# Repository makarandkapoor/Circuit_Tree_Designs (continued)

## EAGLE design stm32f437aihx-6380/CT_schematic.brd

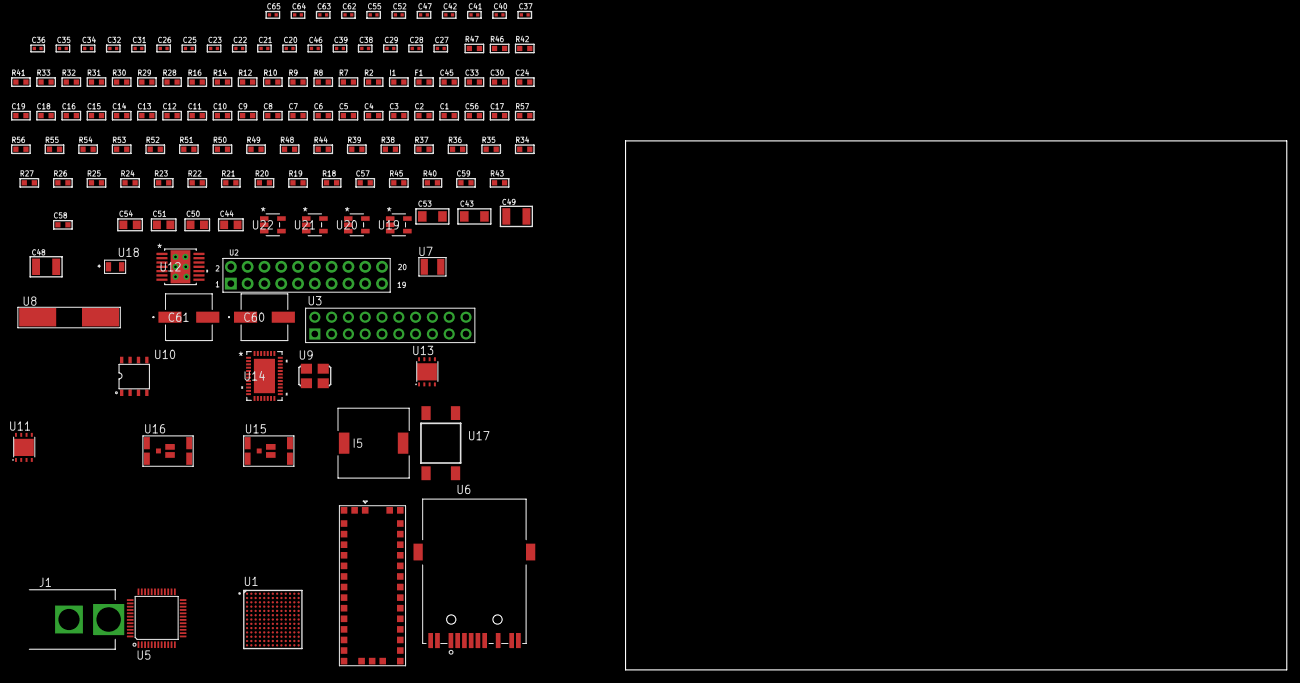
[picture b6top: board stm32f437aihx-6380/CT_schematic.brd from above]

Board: 2 copper layers, 100.0 x 80.0 mm, 139 parts (0 on the bottom side), 100 nets, no tracks yet.

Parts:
C1, C19, C24, C30, C33, C45: 1e-06; C0603
C2, C3, C4, C5, C6, C7, C8, C9, C10, C11, C12, C13, C14, C15, C16: 1e-07; C0603
C17: 4.7e-06; C0603
C18: 1e-08; C0603
C20, C21, C25, C26, C31, C34, C36, C37, C47, C55: 1e-07; C0402
C22, C23: 1e-11; C0402
C27, C28: 2.2e-11; C0402
C29: 2.2e-08; C0402
C32, C35, C40, C41, C42, C52, C62, C63, C64, C65: 1e-08; C0402
C38, C39: 2.7e-11; C0402
C43, C53: 1e-05; C1206
C44, C50, C51, C54: 1e-05; C0805
C46: 3.3e-09; C0402
C48, C49: 2.2e-05; C1210
C56: 2.2e-06; C0603
C57: 2.45e-08; R0603
C58: 2.8258362168397e-09; R0603
C59: 7.105e-09; R0603
C60, C61: 0.0001; EXV-9H
F1: 240.0; L0603
I1: 97.0; R0603
I5: 2.5e-06; DR1040
J1: PJ-037B; PJ-037B_PACKAGE
R2, R42, R47: 1000.0; R0603
R7, R8, R9, R33: 4700.0; R0603
R10, R12, R14, R16: 2200.0; R0603
R18, R19, R20, R21, R22, R23, R24, R25, R26, R27, R34, R35, R36, R37, R38, R39, R48, R50, R51, R54, R55, R56: 10000.0; R0603
R28, R29: 0.1; R0603
R30, R31, R41, R46: 200.0; R0603
R32: 2490.0; R0603
R40, R45: 100000.0; R0603
R43: 71007.101651032; R0603
R44: 22000.0; R0603
R49: 75000.0; R0603
R52, R53: 95300.0; R0603
R57: 48900.0; R0603
U1: STM32F437AIH6; UFBGA169
U2: arducam_ov2640; ARDUCAM
U3: TST-110-05-T-D-RA
U4: M10382
U5: RTL8201FL-VB-CG
U6: 7498011122R
U7: ABS07-32.768KHZ-7-T
U8: ABLS-25.000MHZ-B2F-T
U9: ASFL1-25MHZ-NCS; ASFL1
U10: idt74fct38072; IDT74FCT38072
U11, U13: LP3878SDX-ADJ/NOPB; WSON-8
U12: tps54325PWP; HTSSOP14
U14: LTC2928CUHF#PBF; QFN-38_UHF
U15, U16: IRF8306MTRPbF; IRF8306MTRPBF
U17: 4-1437565-2; SW_4-1437565-2
U18: Q65110A2395; LGM67K-G1J2-24-Z
U19, U20, U21, U22: nc7sz125m5x; NC7SZ125M5X

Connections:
CLK_CRYSTAL_U1_E1: C22.1, U1.E1, U7.1
CLK_CRYSTAL_U1_F1: C23.1, U1.F1, U7.2
CLK_CRYSTAL_U5_42: C39.1, U5.42, U8.1
CLK_CRYSTAL_U5_43: C38.1, U5.43, U8.2
CLK_U1_G2: U1.G2, U10.6
CLK_U2_8: U2.8, U10.7
CLK_U10_3: U9.3, U10.3
GND: C1.2, C2.2, C3.2, C4.2, C5.2, C6.2, C7.2, C8.2, C9.2, C10.2, C11.2, C12.2, C13.2, C14.2, C15.2, C16.2, C17.2, C18.2, C19.2, C20.2, C21.2, C22.2, C23.2, C24.2, C25.2, C26.2, C27.2, C28.2, C29.2, C30.2, C31.2, C32.2, C33.2, C34.2, C35.2, C36.2, C37.2, C38.2, C39.2, C40.2, C41.2, C42.2, C43.2, C44.2, C45.2, C46.2, C48.2, C49.2, C50.2, C51.2, C52.2, C53.2, C54.2, C55.2, C56.2, C57.2, C58.2, C59.2, C60.2, C61.2, C62.2, C63.2, C64.2, C65.2, J1.2, R2.2, R20.2, R27.2, R28.2, R29.2, R32.2, R34.2, R36.2, R37.2, R38.2, R39.2, R42.2, R44.2, R47.2, R49.2, R52.2, R53.2, R54.2, R55.2, R56.2, U1.D7, U1.D11, U1.E7, U1.F5, U1.F6, U1.G7, U1.G9, U1.J1, U1.J2, U1.J6, U1.J7, U1.J10, U2.2, U2.20, U3.4, U3.6, U3.8, U3.10, U3.12, U3.14, U3.16, U3.18, U3.20, U4.2, U4.4, U4.14, U4.17, U4.21, U4.24, U4.26, U4.28, U4.33, U4.34, U4.35, U4.36, U5.7, U5.20, U5.33, U5.47, U6.11, U9.2, U10.4, U10.5, U10.8, U11.3, U11.PAD, U12.5, U12.8, U12.9, U12.15, U13.3, U13.PAD, U14.8, U14.9, U14.10, U14.12, U14.13, U14.24, U14.25, U14.30, U14.32, U14.39, U18.C, U19.2, U19.3, U20.1, U20.3, U21.1, U21.3, U22.1, U22.3
NET_U1_A5: R19.1, U1.A5
NET_U1_B5: R12.1, U1.B5, U4.18
NET_U1_C3: R18.1, U1.C3
NET_U1_C5: R10.1, U1.C5, U4.19
NET_U1_D12: C21.1, U1.D12
NET_U1_H2: R8.1, U1.H2, U21.4
NET_U1_H5: R14.1, U1.H5, U5.30
NET_U1_J4: C18.1, C19.1, F1.1, U1.J3, U1.J4
NET_U1_K2: R16.1, U1.K2, U5.31
NET_U1_L5: R20.1, U1.L5
NET_U1_M1: R21.1, U1.M1
NET_U1_N11: U17.3, U17.4
NET_U2_19: R9.1, U2.19, U22.4
NET_U3_19: R27.1, U3.19
NET_U5_6: C30.1, C31.1, C32.1, I1.1, U5.6, U5.41
NET_U5_10: R37.1, U5.10
NET_U5_29: R7.1, U5.29, U20.4
NET_U5_32: R33.1, U5.32
NET_U5_34: R35.1, U5.34
NET_U5_35: R36.1, U5.35
NET_U5_40: C37.1, U5.40
NET_U5_46: R32.1, U5.46
NET_U5_48: C36.1, U5.48
NET_U6_1: U5.1, U6.1
NET_U6_3: U5.2, U6.3
NET_U6_4: U5.4, U6.4
NET_U6_5: C29.1, U6.2, U6.5
NET_U6_6: U5.5, U6.6
NET_U6_8: R29.1, U6.8
NET_U6_10: R30.1, U6.10
NET_U6_12: R31.1, U6.12
NET_U6_13: R28.1, U6.13, U6.14
NET_U11_1: C42.1, U11.1
NET_U11_6: R41.2, R42.1, U11.6
NET_U11_8: R40.1, U11.8
NET_U12_2: R43.2, R44.1, U12.2
NET_U12_3: C45.1, U12.3
NET_U12_4: C46.1, U12.4
NET_U12_10: C47.1, I5.1, U12.10, U12.11
NET_U12_12: C47.2, U12.12
NET_U13_1: C52.1, U13.1
NET_U13_6: R46.2, R47.1, U13.6
NET_U13_8: R45.1, U13.8
NET_U14_3: R55.1, U14.3
NET_U14_6: R52.1, U14.6
NET_U14_7: R53.1, U14.7
NET_U14_16: R54.1, R57.1, U14.16
NET_U14_18: R51.1, U14.18
NET_U14_19: R50.1, U14.19, U14.20
NET_U14_21: R48.1, R49.1, U14.21, U19.4, U20.2, U21.2, U22.2
NET_U14_26: C58.1, U14.26
NET_U14_27: C57.1, U14.27
NET_U14_28: C59.1, U14.28
NET_U14_38: R56.1, U14.38
NET_U15_3: U14.2, U15.3
NET_U16_3: U14.37, U16.3
NET_U17_1: R2.1, U17.1, U17.2
PROC_DCMI_D0: U1.E8, U2.18
PROC_DCMI_D1: U1.E9, U2.17
PROC_DCMI_D2: U1.B4, U2.16
PROC_DCMI_D3: U1.A4, U2.15
PROC_DCMI_D4: U1.B10, U2.14
PROC_DCMI_D5: U1.A9, U2.13
PROC_DCMI_D6: U1.A2, U2.12
PROC_DCMI_D7: U1.B1, U2.11
PROC_DCMI_D8: U1.C10, U2.10
PROC_DCMI_D9: U1.A10, U2.9
PROC_DCMI_HSYNC: U1.L10, U2.6
PROC_DCMI_PIXCK: U1.N3, U2.7
PROC_DCMI_VSYNC: U1.A3, U2.5
PROC_ETH_COL: U1.K3, U5.38
PROC_ETH_CRS: U1.L2, U5.36
PROC_ETH_RXD3: R38.1, U1.K5, U5.18
PROC_ETH_RX_CLK: U1.K1, U5.19
PROC_ETH_RX_DV: R34.1, U1.K4, U5.13
PROC_ETH_RX_ER: R39.1, U1.E3, U5.39
PROC_ETH_TXD2: U1.H6, U5.25
PROC_ETH_TXD3: U1.B2, U5.26
PROC_ETH_TX_CLK: U1.H7, U5.22
PROC_ETH_TX_EN: U1.B7, U5.27
PROC_SYS_JTCK_SWCLK: R25.1, U1.A11, U3.9
PROC_SYS_JTDI: R23.1, U1.B11, U3.5
PROC_SYS_JTDO_SWO: U1.B6, U3.13
PROC_SYS_JTMS_SWDIO: R24.1, U1.E12, U3.7
PROC_SYS_JTRST: R22.1, U1.A6, U3.3
RST_OUT_U3_SRESET_B: R26.1, U3.15, U19.1
VCC_6V4: C55.1, C56.1, C60.1, C61.1, J1.1, R48.2, R50.2, R51.2, R57.2, U14.11, U14.22, U15.1, U15.2, U15.6, U15.7, U16.1, U16.2, U16.6, U16.7
VCC_S1_6V4: C43.1, C50.1, C51.1, R40.2, U11.4, U12.7, U12.13, U12.14, U15.4, U15.5
VCC_S2_6V4: C53.1, R45.2, U13.4, U16.4, U16.5
VCC_TIER1_1V2: C20.1, C44.1, R41.1, U1.N9, U11.5
VCC_TIER1_3V3: C1.1, C2.1, C3.1, C4.1, C5.1, C6.1, C7.1, C8.1, C9.1, C10.1, C11.1, C12.1, C13.1, C14.1, C15.1, C16.1, C17.1, C24.1, C25.1, C26.1, C27.1, C28.1, C33.1, C34.1, C35.1, C40.1, C41.1, C48.1, C49.1, C62.1, C63.1, C64.1, C65.1, F1.2, I1.2, I5.2, R7.2, R8.2, R9.2, R10.2, R12.2, R14.2, R16.2, R18.2, R19.2, R21.2, R22.2, R23.2, R24.2, R25.2, R26.2, R33.2, R35.2, R43.1, U1.D3, U1.D6, U1.D10, U1.E5, U1.E6, U1.F4, U1.F7, U1.F8, U1.G8, U1.G10, U1.H4, U1.H8, U1.J11, U1.K6, U1.L6, U2.1, U3.1, U3.2, U4.5, U4.25, U4.27, U5.15, U5.21, U5.37, U9.4, U10.1, U10.2, U12.1, U19.5, U20.5, U21.5, U22.5
VCC_TIER2_1V2: C54.1, R46.1, U13.5

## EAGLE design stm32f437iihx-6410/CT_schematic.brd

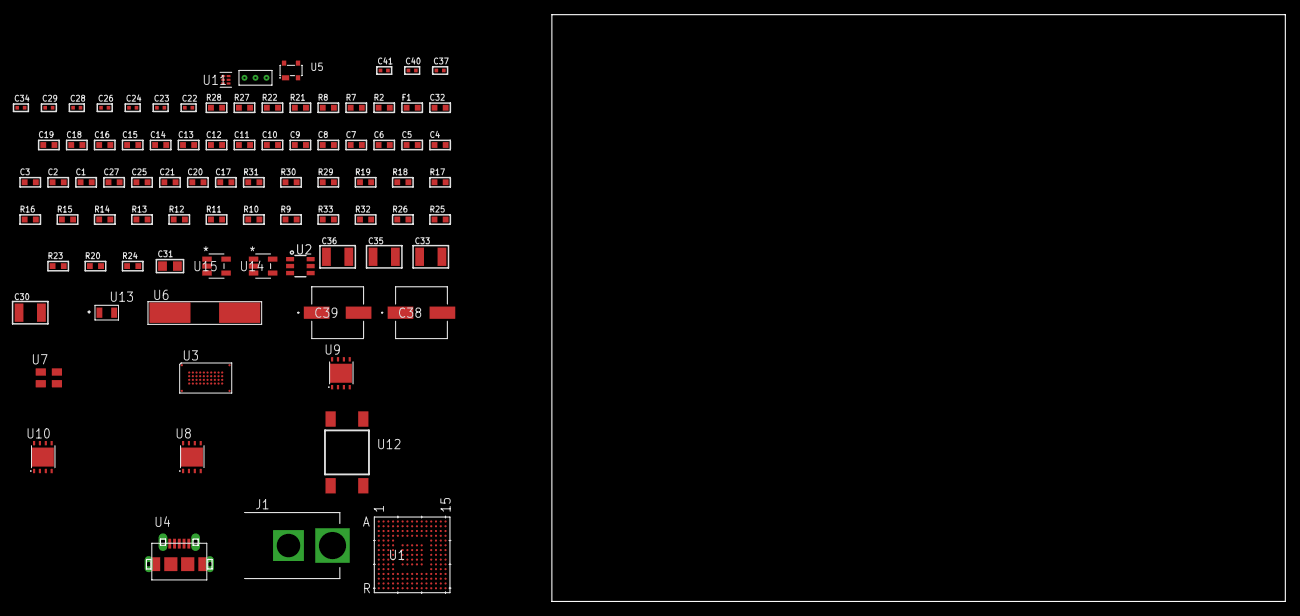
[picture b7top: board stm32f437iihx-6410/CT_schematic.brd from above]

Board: 2 copper layers, 87 parts (0 on the bottom side), 69 nets, no tracks yet.

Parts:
C1, C19: 1e-06; C0603
C2, C3, C4, C5, C6, C7, C8, C9, C10, C11, C12, C13, C14, C15, C16: 1e-07; C0603
C17: 4.7e-06; C0603
C18: 1e-08; C0603
C20, C21, C25, C27: 2.2e-06; C0603
C22, C23: 1e-11; C0402
C24, C26, C37: 1e-07; C0402
C28, C29, C34, C40, C41: 1e-08; C0402
C30, C33, C35, C36: 1e-05; C1210
C31: 1e-05; C0805
C32: 8e-07; R0603
C38, C39: 0.0001; EXV-9H
F1: 240.0; L0603
J1: PJ-037B; PJ-037B_PACKAGE
R2, R22, R28: 1000.0; R0603
R7, R8: 4700.0; R0603
R9: 47000.0; R0603
R10, R11, R12, R13, R14, R15, R16, R17, R18, R19, R29, R30: 10000.0; R0603
R20, R23, R25, R26: 100000.0; R0603
R21: 806.0; R0603
R24: 153694.38; R0603
R27: 3900.0; R0603
R31: 82000.0; R0603
R32: 300000.0; R0603
R33: 120000.0; R0603
U1: STM32F437IIH6; UFBGA176_25
U2: MAX4995AAUT+T; SOT-23-6
U3: S29VS256RABBHW000
U4: 47590-0001; MICRO_USB_AB
U5: prtr5v0u2ax; SOT143B
U6: ABLS-25.000MHZ-B2F-T
U7: ASEK-32.768KHz-ECST; ASEK
U8, U10: LP3878SDX-ADJ/NOPB; WSON-8
U9: LP2951ACSDX/NOPB; WSON-8
U11: TPS3895ADRYR; SON-6
U12: 4-1437565-2; SW_4-1437565-2
U13: Q65110A2395; LGM67K-G1J2-24-Z
U14, U15: nc7sz125m5x; NC7SZ125M5X
U16: Dummy; DUMMY_PACKAGE_185

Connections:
CLK_CRYSTAL_U1_G1: C22.1, U1.G1, U6.1
CLK_CRYSTAL_U1_H1: C23.1, U1.H1, U6.2
CLK_U1_E1: U1.E1, U7.3
GND: C1.2, C2.2, C3.2, C4.2, C5.2, C6.2, C7.2, C8.2, C9.2, C10.2, C11.2, C12.2, C13.2, C14.2, C15.2, C16.2, C17.2, C18.2, C19.2, C20.2, C21.2, C22.2, C23.2, C24.2, C25.2, C26.2, C27.2, C28.2, C29.2, C30.2, C31.2, C32.2, C33.2, C34.2, C35.2, C36.2, C37.2, C38.2, C39.2, C40.2, C41.2, J1.2, R2.2, R9.2, R13.2, R15.2, R22.2, R25.2, R28.2, R31.2, R33.2, U1.D5, U1.D7, U1.D8, U1.D9, U1.F2, U1.F6, U1.F7, U1.F8, U1.F9, U1.F10, U1.F12, U1.G2, U1.G6, U1.G7, U1.G8, U1.G9, U1.G10, U1.G12, U1.H6, U1.H7, U1.H8, U1.H9, U1.H10, U1.H12, U1.J6, U1.J7, U1.J8, U1.J9, U1.J10, U1.K6, U1.K7, U1.K8, U1.K9, U1.K10, U1.M1, U1.M8, U1.M9, U1.N1, U2.2, U3.C5, U3.D12, U3.E3, U3.F5, U4.5, U4.6, U4.7, U4.8, U4.9, U5.1, U7.2, U8.3, U8.PAD, U9.3, U9.4, U9.PAD, U10.3, U10.PAD, U11.2, U13.C, U14.1, U14.3, U15.1, U15.3, U16.1
NET_U1_C6: R10.1, U1.C6
NET_U1_D6: R11.1, U1.D6
NET_U1_F13: C21.1, U1.F13
NET_U1_J1: R8.1, U1.J1, U15.4
NET_U1_L4: R13.1, U1.L4
NET_U1_M6: R12.1, U1.M6
NET_U1_M10: C20.1, U1.M10
NET_U1_R1: C18.1, C19.1, F1.1, U1.P1, U1.R1
NET_U1_R15: U12.3, U12.4
NET_U2_3: R9.1, U2.3
NET_U3_D8: R7.1, U3.D8, U14.4
NET_U8_1: C29.1, U8.1
NET_U8_6: R21.2, R22.1, U8.6
NET_U8_8: R20.1, U8.8
NET_U9_5: R23.1, U9.5
NET_U9_7: R24.2, R25.1, U9.7
NET_U10_1: C34.1, U10.1
NET_U10_6: R27.2, R28.1, U10.6
NET_U10_8: R26.1, U10.8
NET_U11_1: R30.1, R31.1, U11.1
NET_U11_3: R32.2, R33.1, U11.3
NET_U11_4: R29.1, U11.4, U14.2, U15.2
NET_U12_1: R2.1, U12.1, U12.2
PROC_ADC1_IN3: U1.R2, U16.2
PROC_ADC1_IN4: U1.N4, U16.3
PROC_FMC_A16: U1.N14, U3.D4
PROC_FMC_A17: U1.N13, U3.C11
PROC_FMC_A18: U1.M15, U3.D10
PROC_FMC_A19: U1.A1, U3.C10
PROC_FMC_A20: U1.B1, U3.D5
PROC_FMC_A21: U1.B2, U3.C4
PROC_FMC_A22: U1.B3, U3.C12
PROC_FMC_A23: U1.A2, U3.D7
PROC_FMC_CLK: U1.D11, U3.C6
PROC_FMC_D0: U1.M14, U3.F3
PROC_FMC_D1: U1.L14, U3.F4
PROC_FMC_D2: U1.B12, U3.E6
PROC_FMC_D3: U1.C12, U3.E7
PROC_FMC_D4: U1.R8, U3.F8
PROC_FMC_D5: U1.P8, U3.F9
PROC_FMC_D6: U1.P9, U3.E10
PROC_FMC_D7: U1.R9, U3.E11
PROC_FMC_D8: U1.P10, U3.E4
PROC_FMC_D9: U1.R10, U3.E5
PROC_FMC_D10: U1.N11, U3.F6
PROC_FMC_D11: U1.P11, U3.F7
PROC_FMC_D12: U1.R11, U3.E8
PROC_FMC_D13: U1.P15, U3.E9
PROC_FMC_D14: U1.P14, U3.F11
PROC_FMC_D15: U1.N15, U3.F12
PROC_FMC_NE2: R17.1, U1.C10, U3.D11
PROC_FMC_NL: U1.B5, U3.D6
PROC_FMC_NOE: R19.1, U1.D10, U3.E12
PROC_FMC_NWAIT: R16.1, U1.B11, U3.C3
PROC_FMC_NWE: R18.1, U1.C11, U3.C8
PROC_GPIO_TO_U1_USB_FAULT: R14.1, U1.A4, U2.6
PROC_GPIO_TO_U1_VBUS_EN: R15.1, U1.A3, U2.4
PROC_USB_OTG_FS_DM: U1.C15, U4.2, U5.3
PROC_USB_OTG_FS_DP: U1.B15, U4.3, U5.2
PROC_USB_OTG_FS_ID: U1.D15, U4.4
PROC_USB_OTG_FS_VBUS: U1.E15, U2.1, U4.1, U5.4
VCC_S1_12V3: C30.1, C32.1, C35.1, C38.1, C39.1, J1.1, R20.2, R26.2, U8.4, U9.8, U10.4
VCC_TIER1_1V8: C1.1, C2.1, C3.1, C4.1, C5.1, C6.1, C7.1, C8.1, C9.1, C10.1, C11.1, C12.1, C13.1, C14.1, C15.1, C16.1, C17.1, C24.1, C25.1, C26.1, C27.1, C31.1, C37.1, C40.1, C41.1, F1.2, R7.2, R8.2, R10.2, R11.2, R12.2, R14.2, R16.2, R17.2, R18.2, R19.2, R21.1, R29.2, R30.2, R32.1, U1.C1, U1.C5, U1.C7, U1.C8, U1.C9, U1.F3, U1.G3, U1.G13, U1.H13, U1.J12, U1.J13, U1.K4, U1.N8, U1.N9, U1.N10, U3.C7, U3.D3, U3.F10, U8.5, U11.6, U14.5, U15.5
VCC_TIER1_3V3: C28.1, C33.1, R23.2, R24.1, U7.4, U9.1
VCC_TIER1_5V0: C36.1, R27.1, U2.5, U10.5

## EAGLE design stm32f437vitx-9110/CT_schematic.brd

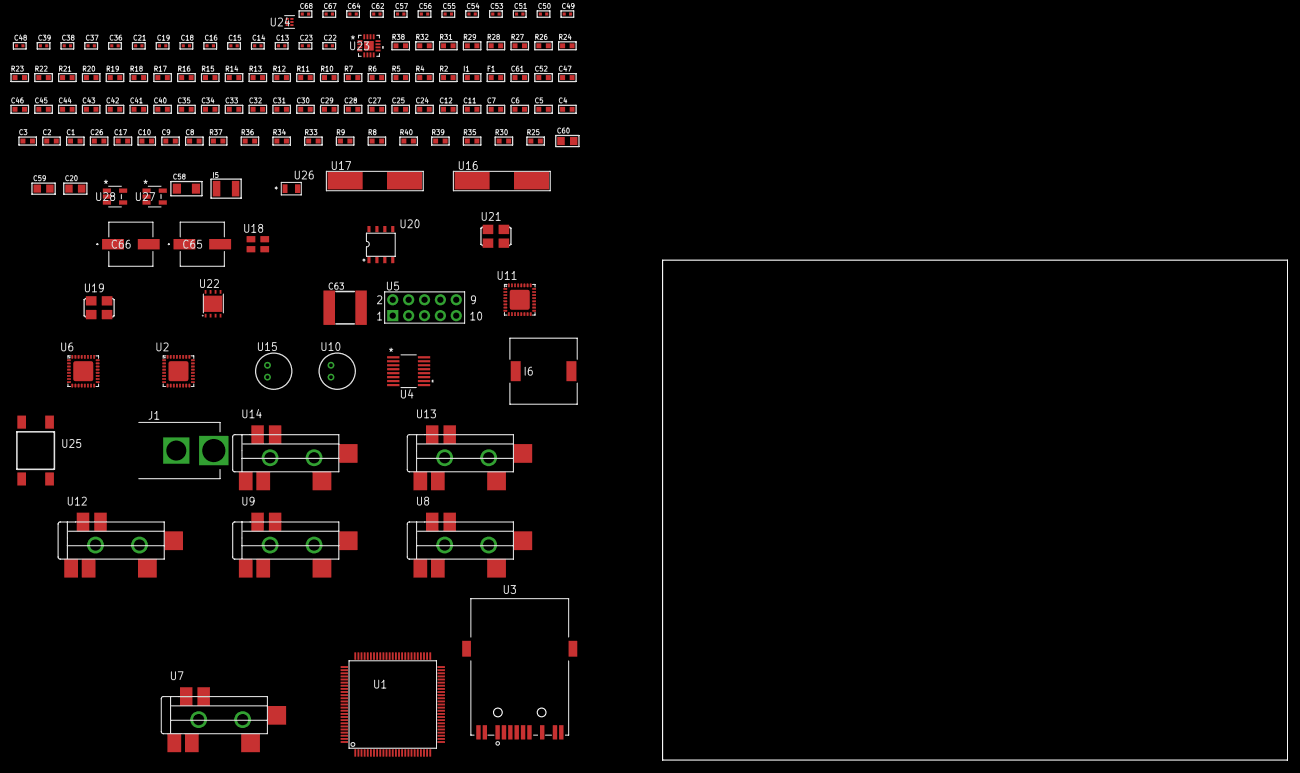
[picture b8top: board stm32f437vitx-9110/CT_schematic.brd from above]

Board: 2 copper layers, 100.0 x 80.0 mm, 139 parts (0 on the bottom side), 108 nets, no tracks yet.

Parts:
C1, C12, C24, C25, C27, C28, C29, C30, C31, C32, C33, C34, C35, C40, C41, C42, C43, C44, C45, C46, C47, C52, C61: 1e-06; C0603
C2, C3, C4, C5, C6, C7: 1e-07; C0603
C8: 4.7e-06; C0603
C9, C10, C17: 2.2e-06; C0603
C11: 1e-08; C0603
C13, C14: 1e-11; C0402
C15, C16, C18, C19, C21, C36, C37, C38, C39, C48, C49, C50, C51, C62, C64: 1e-07; C0402
C20, C59, C60: 1e-05; C0805
C22, C23: 2.2e-11; C0402
C26: 2.2e-07; C0603
C53, C54, C55, C56, C57, C67, C68: 1e-08; C0402
C58: 1e-05; C1206
C63: 6.8e-05; 2220
C65, C66: 0.0001; EXV-9H
F1: 240.0; L0603
I1: 97.0; R0603
I5: 1e-05; L1210
I6: 3.8e-06; DR1040
J1: PJ-037B; PJ-037B_PACKAGE
R2, R17, R19, R21, R32: 1000.0; R0603
R4, R5, R15, R16, R18, R20, R22, R23, R24: 4700.0; R0603
R6, R7: 2200.0; R0603
R8, R9, R36, R37: 10000.0; R0603
R10, R11: 0.1; R0603
R12, R31: 200.0; R0603
R13: 220.0; R0603
R14: 6490.0; R0603
R25, R30: 100000.0; R0603
R26, R27, R28, R29: 1270.0; R0603
R33: 20000.0; R0603
R34: 91000.0; R0603
R35: 300000.0; R0603
R38: 9100.0; R0603
R39: 680000.0; R0603
R40: 120000.0; R0603
U1: STM32F437VIT6; LQFP100
U2: KSZ8081RNBIA-TR; QFN-32
U3: 7498011122R
U4: LTC2804CGN-1#PBF; SSOP-16
U5: HTSS-105-01-G-D
U6, U11: SGTL5000XNAA3; QFN-32
U7, U8, U9, U12, U13, U14: SJ-43515TS-SMT-TR
U10, U15: WM-64PCT; WM-64PC
U16, U17: ABLS-25.000MHZ-B2F-T
U18: ASEK-32.768KHz-ECST; ASEK
U19: ASFL-24.57MHZ-NCS; ASFL1
U20: idt74fct38072; IDT74FCT38072
U21: ASFL1-50MHZ-NCS; ASFL1
U22: LP3878SDX-ADJ/NOPB; WSON-8
U23: LTC3601EUD#PBF; QFN-16_EP
U24: TPS3895ADRYR; SON-6
U25: 4-1437565-2; SW_4-1437565-2
U26: Q65110A2395; LGM67K-G1J2-24-Z
U27, U28: nc7sz125m5x; NC7SZ125M5X

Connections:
CLK_CRYSTAL_U1_12: C13.1, U1.12, U16.1
CLK_CRYSTAL_U1_13: C14.1, U1.13, U16.2
CLK_CRYSTAL_U2_8: C22.1, U2.8, U17.2
CLK_CRYSTAL_U2_9: C23.1, U2.9, U17.1
CLK_U1_8: U1.8, U18.3
CLK_U1_24: U1.24, U21.3
CLK_U6_21: U6.21, U20.7
CLK_U11_21: U11.21, U20.6
CLK_U20_3: U19.3, U20.3
GND: C1.2, C2.2, C3.2, C4.2, C5.2, C6.2, C7.2, C8.2, C9.2, C10.2, C11.2, C12.2, C13.2, C14.2, C15.2, C16.2, C17.2, C18.2, C19.2, C20.2, C21.2, C22.2, C23.2, C24.2, C25.2, C27.2, C28.2, C36.2, C37.2, C38.2, C39.2, C40.2, C48.2, C49.2, C50.2, C51.2, C52.2, C53.2, C54.2, C55.2, C56.2, C57.2, C58.2, C59.2, C60.2, C61.2, C63.1, C63.2, C64.2, C65.2, C66.2, C67.2, C68.2, J1.2, R2.2, R9.2, R10.2, R11.2, R14.2, R16.2, R17.2, R19.2, R21.2, R27.2, R29.2, R32.2, R33.2, R35.2, R38.2, R40.2, U1.10, U1.20, U1.27, U1.74, U1.99, U2.1, U2.EXP, U3.1, U3.10, U4.8, U5.9, U6.1, U6.3, U6.7, U6.EXP, U8.1, U9.1, U10.2, U11.1, U11.3, U11.7, U11.EXP, U13.1, U14.1, U15.2, U18.2, U19.2, U20.4, U20.5, U20.8, U21.2, U22.3, U22.PAD, U23.1, U23.9, U23.17, U24.2, U26.C, U27.1, U27.3, U28.1, U28.3
NET_U1_14: R5.1, U1.14, U28.4
NET_U1_16: R6.1, U1.16, U2.12
NET_U1_22: C11.1, C12.1, F1.1, U1.21, U1.22
NET_U1_25: R7.1, U1.25, U2.11
NET_U1_37: R9.1, U1.37
NET_U1_49: C9.1, U1.49
NET_U1_73: C10.1, U1.73
NET_U1_94: R8.1, U1.94
NET_U1_98: U25.3, U25.4
NET_U2_2: C17.1, C18.1, U2.2
NET_U2_3: C19.1, I1.1, U2.3
NET_U2_10: R14.1, U2.10
NET_U2_13: R17.1, U2.13
NET_U2_14: R18.1, U2.14
NET_U2_19: R16.1, U2.19
NET_U2_20: R22.1, U2.20
NET_U2_21: R15.1, U2.21
NET_U2_28: R20.1, U2.28
NET_U2_29: R21.1, U2.29
NET_U2_31: R23.1, U2.31
NET_U2_32: R4.1, U2.32, U27.4
NET_U3_1: U2.7, U3.1
NET_U3_2: C15.1, U3.2
NET_U3_3: U2.6, U3.3
NET_U3_4: U2.5, U3.4
NET_U3_5: C16.1, U3.5
NET_U3_6: U2.4, U3.6
NET_U3_8: R11.1, U3.8
NET_U3_9: R12.1, U3.9
NET_U3_12: R13.1, U3.12
NET_U3_13: R10.1, U3.13, U3.14
NET_U4_6: C24.1, U4.6
NET_U4_7: C26.1, I5.2, U4.7
NET_U4_9: C25.1, U4.9
NET_U4_10: C26.2, U4.10
NET_U4_11: R25.1, U4.11
NET_U5_3: U4.1, U5.3
NET_U5_4: U4.2, U5.4
NET_U5_5: U4.3, U5.5
NET_U5_6: U4.4, U5.6
NET_U6_10: C39.1, U6.10
NET_U6_29: R26.1, U6.29
NET_U6_31: R27.1, U6.31
NET_U7_1: U6.4, U7.1
NET_U7_2: U6.2, U7.2
NET_U7_5: U6.6, U7.5
NET_U8_2: C30.1, U8.2
NET_U8_5: C29.1, U8.5
NET_U9_2: C32.1, C33.1, U9.2
NET_U9_5: C31.1, U9.5
NET_U9_13: C32.2, C33.2
NET_U10_1: C34.1, C35.1, C40.1, U6.16, U10.1
NET_U10_15: C34.2, C35.2
NET_U11_10: C51.1, U11.10
NET_U11_29: R28.1, U11.29
NET_U11_31: R29.1, U11.31
NET_U12_1: U11.4, U12.1
NET_U12_2: U11.2, U12.2
NET_U12_5: U11.6, U12.5
NET_U13_2: C42.1, U13.2
NET_U13_5: C41.1, U13.5
NET_U14_2: C44.1, C45.1, U14.2
NET_U14_5: C43.1, U14.5
NET_U14_13: C44.2, C45.2
NET_U15_1: C46.1, C47.1, C52.1, U11.16, U15.1
NET_U15_15: C46.2, C47.2
NET_U22_1: C57.1, U22.1
NET_U22_6: R31.2, R32.1, U22.6
NET_U22_8: R30.1, U22.8
NET_U23_3: C62.2, I6.1, U23.3, U23.4
NET_U23_6: C62.1, U23.6
NET_U23_7: C61.1, U23.7, U23.12
NET_U23_10: R35.1, U23.10
NET_U23_11: R33.1, R34.1, U23.11
NET_U23_ATNET_3: I6.2, R34.2
NET_U24_1: R37.1, R38.1, U24.1
NET_U24_3: R39.2, R40.1, U24.3
NET_U24_4: R36.1, U24.4, U27.2, U28.2
NET_U25_1: R2.1, U25.1, U25.2
PROC_ETH_CRS_DV: U1.32, U2.18
PROC_ETH_RXD0: R24.1, U1.33, U2.16
PROC_ETH_RXD1: R19.1, U1.34, U2.15
PROC_ETH_TXD0: U1.51, U2.24
PROC_ETH_TXD1: U1.52, U2.25
PROC_ETH_TX_EN: U1.48, U2.23
PROC_I2S2_CK: U1.47, U6.24
PROC_I2S2_EXT_SD: U1.17, U6.25
PROC_I2S2_SD: U1.18, U6.26
PROC_I2S2_WS: U1.96, U6.23
PROC_I2S3_CK: U1.78, U11.24
PROC_I2S3_EXT_SD: U1.90, U11.25
PROC_I2S3_SD: U1.80, U11.26
PROC_I2S3_WS: U1.29, U11.23
PROC_UART4_RX: U1.79, U4.16
PROC_UART4_TX: U1.23, U4.14
VCC_S1_9V9: C58.1, C60.1, C65.1, C66.1, J1.1, R30.2, U22.4, U23.15, U23.16
VCC_TIER1_1V2: C36.1, C48.1, C59.1, R31.1, U6.30, U11.30, U22.5
VCC_TIER1_3V3: C1.1, C2.1, C3.1, C4.1, C5.1, C6.1, C7.1, C8.1, C20.1, C21.1, C27.1, C28.1, C37.1, C38.1, C49.1, C50.1, C53.1, C54.1, C55.1, C56.1, C63.2, C64.1, C67.1, C68.1, F1.2, I1.2, I5.1, I6.2, R4.2, R5.2, R6.2, R7.2, R8.2, R15.2, R18.2, R20.2, R22.2, R23.2, R24.2, R25.2, R26.2, R28.2, R34.2, R36.2, R37.2, R39.1, U1.6, U1.11, U1.19, U1.28, U1.50, U1.75, U1.100, U2.17, U4.5, U4.12, U6.5, U6.20, U11.5, U11.20, U18.4, U19.4, U20.1, U20.2, U21.4, U23.8, U24.6, U27.5, U28.5
